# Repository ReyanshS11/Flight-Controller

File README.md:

# Express Flight Controller
Express is a feature-packed flight controller for drones.

## Key Features
- STM32H743VIT6 microcontroller for speed and performance
- ICM-45686 IMU for precise motion tracking
- BMP581 barometer for accurate altitude data
- NEO-M8U-06B GPS for pinpoint positioning
- Ra-02 RF transmitter for communication
- MicroSD slot for data storage
- USB-C port for program and data transfer
- 2s LiPo battery support and charging with BQ25887RGER
- Connectors for ESC and camera

## Design Features
- The complete flight controller fits within a 70x65mm space.
- Comprised of two layers, front and back copper
- Silkscreen for organization and ease of use

## Schematic and Design

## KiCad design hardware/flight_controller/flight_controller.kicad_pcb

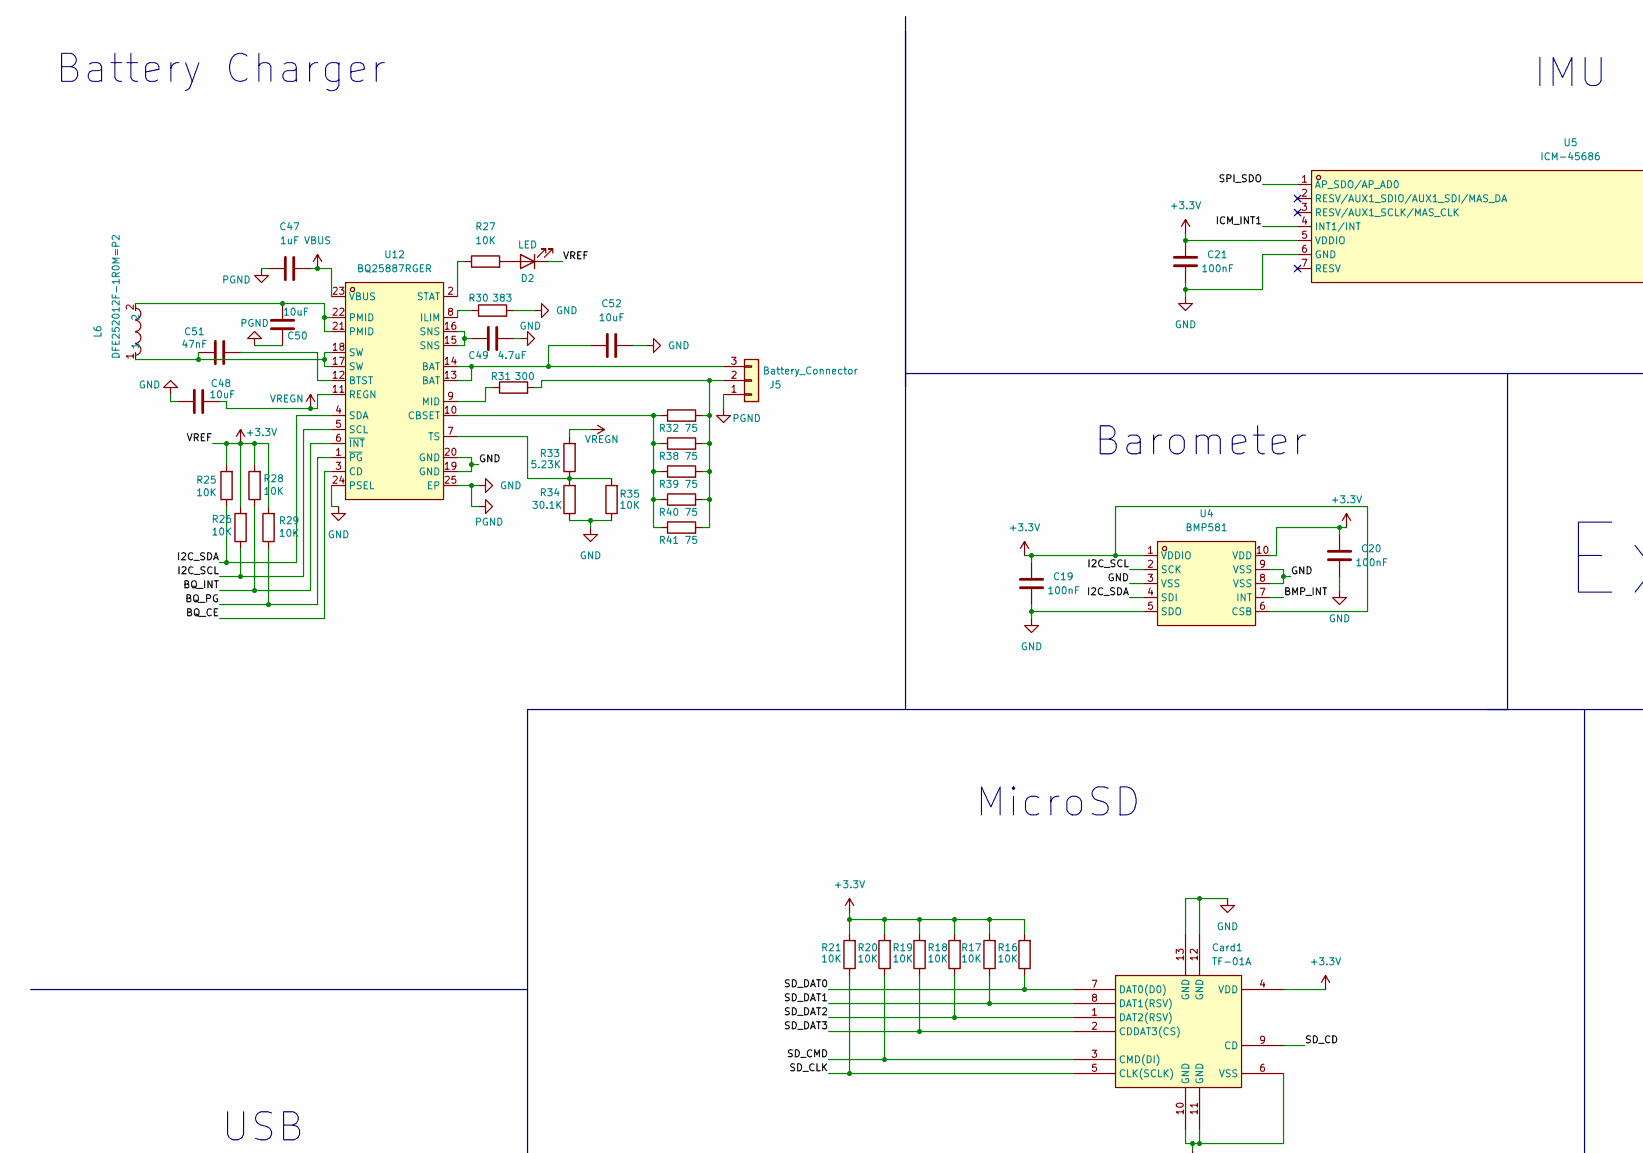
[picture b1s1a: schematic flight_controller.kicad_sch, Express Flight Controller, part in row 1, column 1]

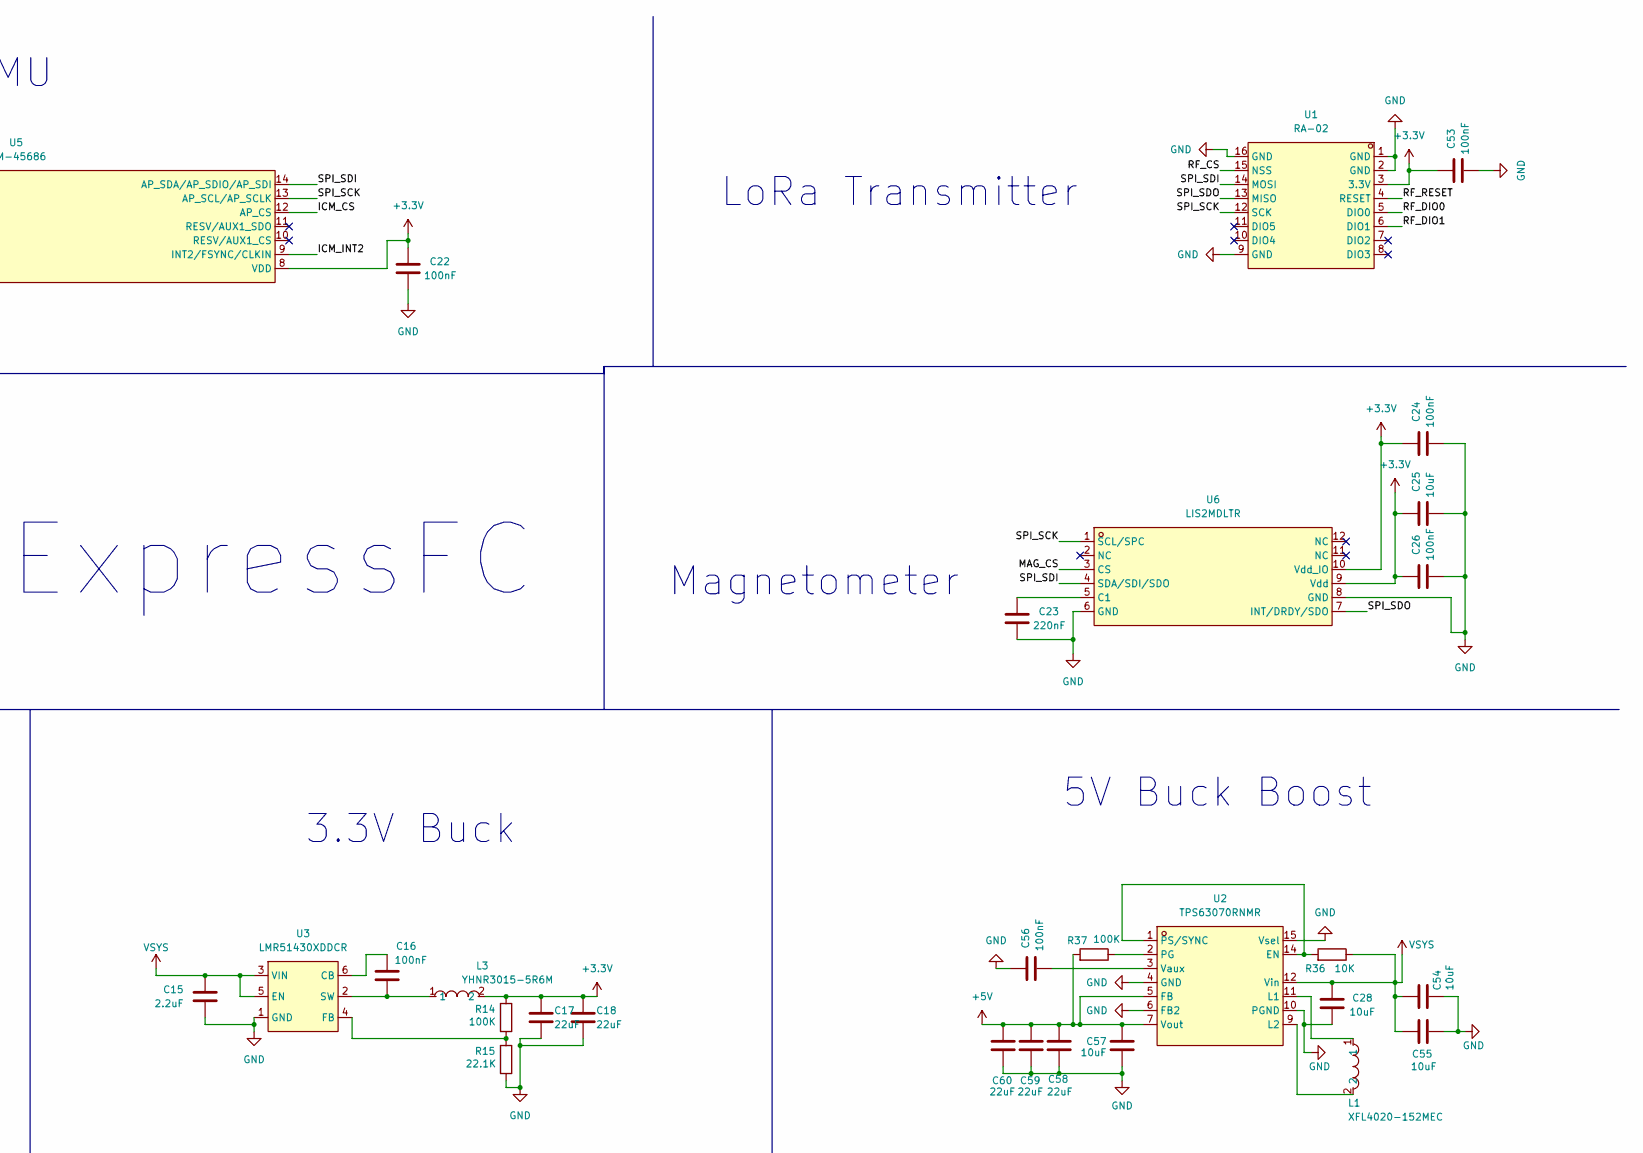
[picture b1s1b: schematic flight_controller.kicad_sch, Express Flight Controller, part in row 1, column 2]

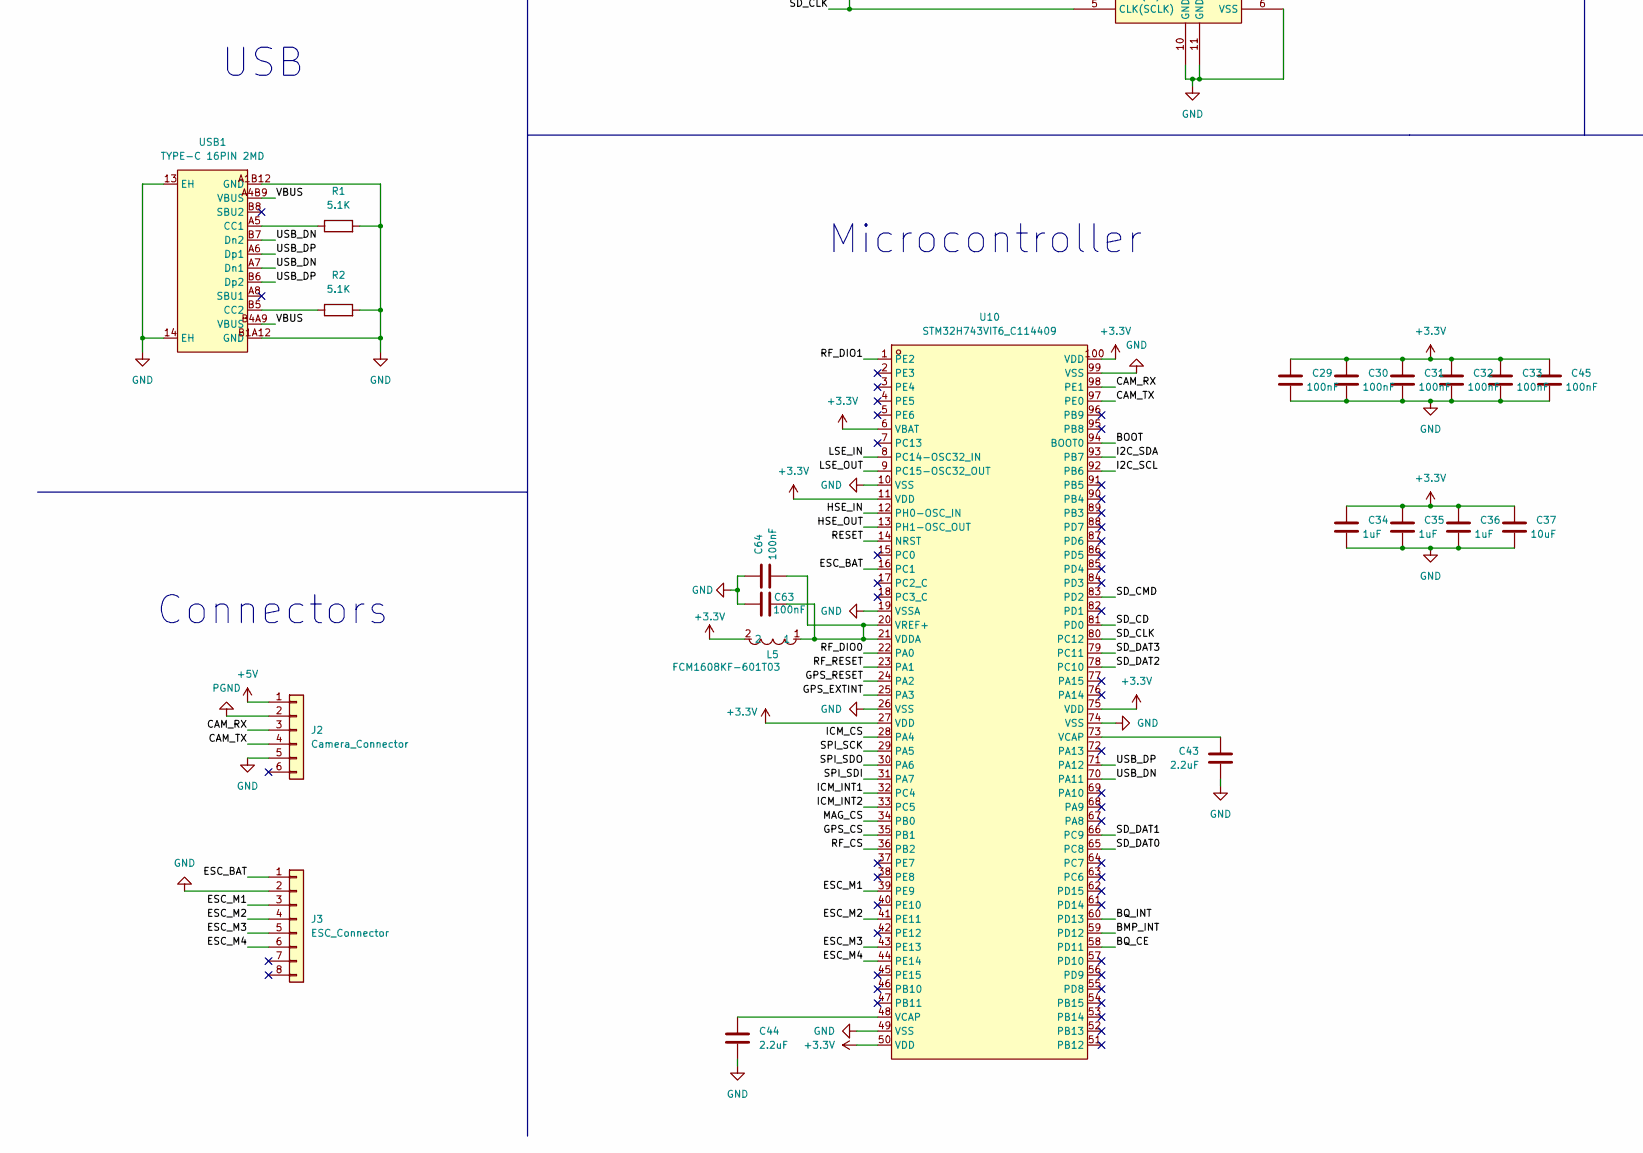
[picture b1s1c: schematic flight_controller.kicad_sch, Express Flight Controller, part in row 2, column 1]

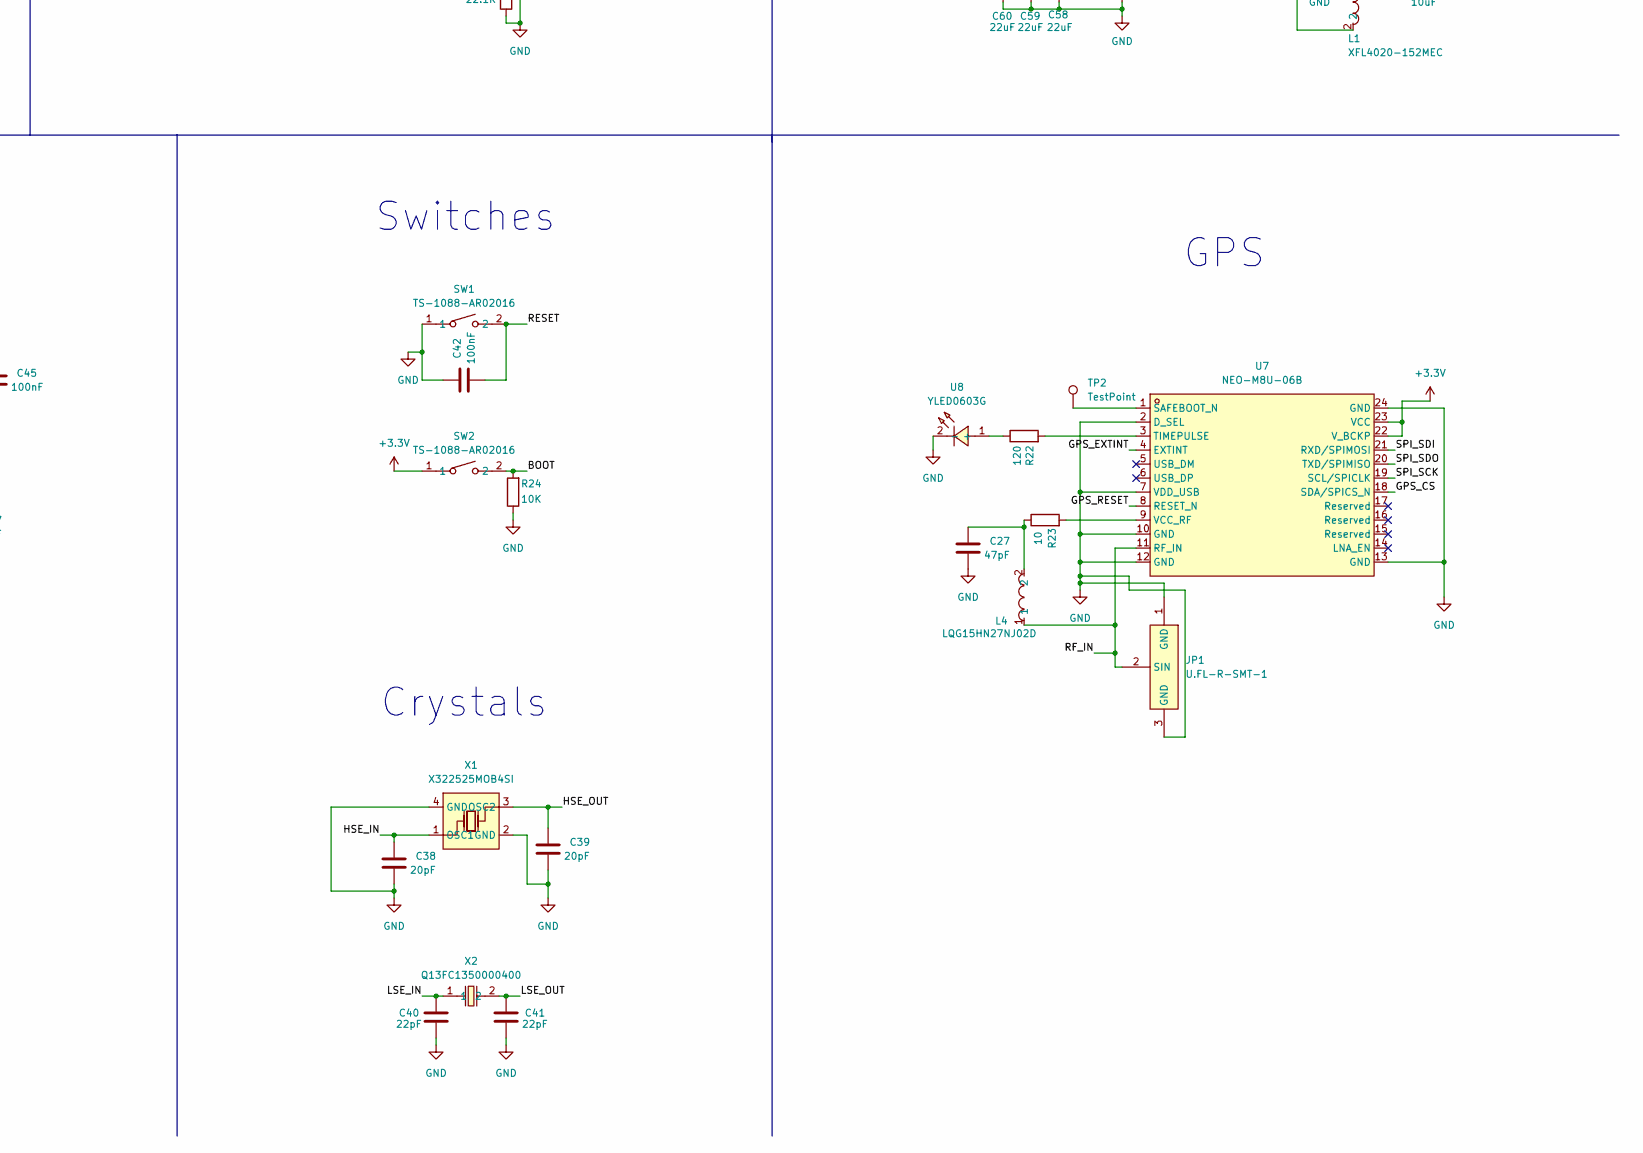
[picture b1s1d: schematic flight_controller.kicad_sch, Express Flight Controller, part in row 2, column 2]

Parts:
C15: 2.2uF; C_0603_1608Metric
C16, C19, C20, C21, C22, C24, C26, C29, C30, C31, C32, C33, C42, C45, C53, C63, C64: 100nF; C_0201_0603Metric
C17, C18, C58, C59, C60: 22uF; C_0805_2012Metric
C23: 220nF; C_0201_0603Metric
C25, C37, C48, C50, C57: 10uF; C_0402_1005Metric
C27: 47pF; C_0201_0603Metric
C28: 10uF; C_0201_0603Metric
C34, C35, C36, C47: 1uF; C_0402_1005Metric
C38, C39: 20pF; C_0201_0603Metric
C40, C41: 22pF; C_0201_0603Metric
C43, C44: 2.2uF; C_0402_1005Metric
C49: 4.7uF; C_0402_1005Metric
C51: 47nF; C_0201_0603Metric
C52: 10uF; C_0603_1608Metric
C54, C55: 10uF; C_0805_2012Metric
C56: 100nF; C_0402_1005Metric
Card1: TF-01A; TF-SMD_TF-01A; MPN TF-01A; LCSC Part C91145
D2: LED; LED_0402_1005Metric
J2: Camera_Connector; JST_SH_SM06B-SRSS-TB_1x06-1MP_P1.00mm_Horizontal
J3: ESC_Connector; JST_SH_SM08B-SRSS-TB_1x08-1MP_P1.00mm_Horizontal
J5: Battery_Connector; JST_XH_S3B-XH-A_1x03_P2.50mm_Horizontal
JP1: U.FL-R-SMT-1; ANT-SMD_UFL-R-SMT-1-10; MPN U.FL-R-SMT-1(10); LCSC Part C88373
L1: XFL4020-152MEC; IND-SMD_L4.0-W4.0-A; MPN XFL4020-152MEC; LCSC Part C3033018
L3: YHNR3015-5R6M; IND-SMD_L3.0-W3.0; MPN YHNR3015-5R6M; LCSC Part C18236327
L4: LQG15HN27NJ02D; L0402; MPN LQG15HN27NJ02D; LCSC Part C115488
L5: FCM1608KF-601T03; L0603; MPN FCM1608KF-601T03; LCSC Part C141723
L6: DFE252012F-1R0M=P2; L2520; MPN DFE252012F-1R0M=P2; LCSC Part C435392
R1, R2: 5.1K; R_0201_0603Metric
R14, R37: 100K; R_0603_1608Metric
R15: 22.1K; R_0402_1005Metric
R16, R17, R18, R19, R20, R21, R24, R25, R26, R27, R28, R29, R35, R36: 10K; R_0603_1608Metric
R22: 120; R_0201_0603Metric
R23: 10; R_0201_0603Metric
R30: 383; R_0603_1608Metric
R31: 300; R_0603_1608Metric
R32, R38, R39, R40, R41: 75; R_1206_3216Metric
R33: 5.23K; R_0603_1608Metric
R34: 30.1K; R_0603_1608Metric
SW1, SW2: TS-1088-AR02016; SW-SMD_L3.9-W3.0-P4.45; MPN TS-1088-AR02016; LCSC Part C720477
TP2: TestPoint; TestPoint_Pad_1.0x1.0mm
U1: RA-02; WIRELM-SMD_RA-02-BL; MPN Ra-02; LCSC Part C90039
U2: TPS63070RNMR; VQFN-15_L3.0-W2.5-P0.50-BL; MPN TPS63070RNMR; LCSC Part C109322
U3: LMR51430XDDCR; SOT-23-6_L2.9-W1.6-P0.95-LS2.8-BL; MPN LMR51430XDDCR; LCSC Part C5185863
U4: BMP581; LGA-10_L2.0-W2.0-P0.50-TL_BMP581; MPN BMP581; LCSC Part C5362283
U5: ICM-45686; LGA-14_L3.0-W2.5-P0.50-TL; MPN ICM-45686; LCSC Part C22459454
U6: LIS2MDLTR; VLGA-12_L2.0-W2.0-P0.50-BL; MPN LIS2MDLTR; LCSC Part C919695
U7: NEO-M8U-06B; GPSM-SMD_24P-L16.0-W12.2-P1.10-TL; MPN NEO-M8U-06B; LCSC Part C7009321
U8: YLED0603G; LED0603-FD; MPN YLED0603G; LCSC Part C19273151
U10: STM32H743VIT6_C114409; LQFP-100_L14.0-W14.0-P0.50-LS16.0-BL; MPN STM32H743VIT6; LCSC Part C114409
U12: BQ25887RGER; VFQFPN-24_L4.0-W4.0-P0.50-BL-EP2.8; MPN BQ25887RGER; LCSC Part C2761614
USB1: TYPE-C 16PIN 2MD; USB-C-SMD_TYPE-C-16PIN-2MD-073; MPN TYPE-C 16PIN 2MD(073); LCSC Part C2765186
X1: X322525MOB4SI; CRYSTAL-SMD_4P-L3.2-W2.5-BL; MPN X322525MOB4SI; LCSC Part C9006
X2: Q13FC1350000400; FC-135R_L3.2-W1.5; MPN Q13FC13500004; LCSC Part C32346

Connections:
+3.3V: C17.1, C18.1, C19.1, C20.1, C21.1, C22.1, C24.1, C25.1, C26.1, C29.1, C30.1, C31.1, C32.1, C33.1, C34.1, C35.1, C36.1, C37.1, C45.1, C53.1, Card1.4 (VDD), D2.1 (K), L3.2, L5.2, R14.2, R16.2, R17.2, R18.2, R19.2, R20.2, R21.2, R25.2, R26.2, R28.2, R29.2, SW2.1, U1.3 (3.3V), U4.1 (VDDIO), U4.6 (CSB), U4.10 (VDD), U5.5 (VDDIO), U5.8 (VDD), U6.9 (Vdd), U6.10 (Vdd_IO), U7.22 (V_BCKP), U7.23 (VCC), U10.6 (VBAT), U10.11 (VDD), U10.27 (VDD), U10.50 (VDD), U10.75 (VDD), U10.100 (VDD)
+5V: C57.1, C58.2, C59.2, C60.2, J2.1, R37.2, U2.5 (FB), U2.7 (Vout)
/BMP_INT: U4.7 (INT), U10.59 (PD12)
/BOOT: R24.2, SW2.2, U10.94 (BOOT0)
/BQ_CE: U10.58 (PD11), U12.3 (CD)
/BQ_INT: R28.1, U10.60 (PD13), U12.6 (~INT)
/BQ_PG: R29.1, U12.1 (~PG)
/CAM_RX: J2.3, U10.98 (PE1)
/CAM_TX: J2.4, U10.97 (PE0)
/ESC_BAT: J3.1, U10.16 (PC1)
/ESC_M1: J3.3, U10.39 (PE9)
/ESC_M2: J3.4, U10.41 (PE11)
/ESC_M3: J3.5, U10.43 (PE13)
/ESC_M4: J3.6, U10.44 (PE14)
/GPS_CS: U7.18 (SDA/SPICS_N), U10.35 (PB1)
/GPS_EXTINT: U7.4 (EXTINT), U10.25 (PA3)
/GPS_RESET: U7.8 (RESET_N), U10.24 (PA2)
/HSE_IN: C38.1, U10.12 (PH0-OSC_IN), X1.1 (OSC1)
/HSE_OUT: C39.1, U10.13 (PH1-OSC_OUT), X1.3 (OSC2)
/I2C_SCL: R26.1, U4.2 (SCK), U10.92 (PB6), U12.5 (SCL)
/I2C_SDA: R25.1, U4.4 (SDI), U10.93 (PB7), U12.4 (SDA)
/ICM_CS: U5.12 (AP_CS), U10.28 (PA4)
/ICM_INT1: U5.4 (INT1/INT), U10.32 (PC4)
/ICM_INT2: U5.9 (INT2/FSYNC/CLKIN), U10.33 (PC5)
/LSE_IN: C40.1, U10.8 (PC14-OSC32_IN), X2.1
/LSE_OUT: C41.1, U10.9 (PC15-OSC32_OUT), X2.2
/MAG_CS: U6.3 (CS), U10.34 (PB0)
/RESET: C42.2, SW1.2, U10.14 (NRST)
/RF_CS: U1.15 (NSS), U10.36 (PB2)
/RF_DIO0: U1.5 (DIO0), U10.22 (PA0)
/RF_DIO1: U1.6 (DIO1), U10.1 (PE2)
/RF_IN: JP1.2 (SIN), L4.1, U7.11 (RF_IN)
/RF_RESET: U1.4 (RESET), U10.23 (PA1)
/SD_CD: Card1.9 (CD), U10.81 (PD0)
/SD_CLK: Card1.5 (CLK(SCLK)), R21.1, U10.80 (PC12)
/SD_CMD: Card1.3 (CMD(DI)), R20.1, U10.83 (PD2)
/SD_DAT0: Card1.7 (DAT0(D0)), R16.1, U10.65 (PC8)
/SD_DAT1: Card1.8 (DAT1(RSV)), R17.1, U10.66 (PC9)
/SD_DAT2: Card1.1 (DAT2(RSV)), R18.1, U10.78 (PC10)
/SD_DAT3: Card1.2 (CDDAT3(CS)), R19.1, U10.79 (PC11)
/SPI_SCK: U1.12 (SCK), U5.13 (AP_SCL/AP_SCLK), U6.1 (SCL/SPC), U7.19 (SCL/SPICLK), U10.29 (PA5)
/SPI_SDI: U1.14 (MOSI), U5.14 (AP_SDA/AP_SDIO/AP_SDI), U6.4 (SDA/SDI/SDO), U7.21 (RXD/SPIMOSI), U10.31 (PA7)
/SPI_SDO: U1.13 (MISO), U5.1 (AP_SDO/AP_AD0), U6.7 (INT/DRDY/SDO), U7.20 (TXD/SPIMISO), U10.30 (PA6)
/USB_DN: U10.70 (PA11), USB1.A7 (Dn1), USB1.B7 (Dn2)
/USB_DP: U10.71 (PA12), USB1.A6 (Dp1), USB1.B6 (Dp2)
GND: C15.2, C17.2, C18.2, C19.2, C20.2, C21.2, C22.2, C23.2, C24.2, C25.2, C26.2, C27.2, C28.2, C29.2, C30.2, C31.2, C32.2, C33.2, C34.2, C35.2, C36.2, C37.2, C38.2, C39.2, C40.2, C41.2, C42.1, C43.2, C44.2, C45.2, C47.1, C48.1, C49.2, C50.1, C52.2, C53.2, C54.2, C55.2, C56.1, C57.2, C58.1, C59.1, C60.1, C63.1, C64.1, Card1.6 (VSS), Card1.10 (GND), Card1.11 (GND), Card1.12 (GND), Card1.13 (GND), J2.2, J2.5, J3.2, J5.1, JP1.1 (GND), JP1.3 (GND), R1.2, R2.2, R15.1, R24.1, R30.2, R34.1, R35.1, SW1.1, U1.1 (GND), U1.2 (GND), U1.9 (GND), U1.16 (GND), U2.4 (GND), U2.6 (FB2), U2.10 (PGND), U2.15 (Vsel), U3.1 (GND), U4.3 (VSS), U4.5 (SDO), U4.8 (VSS), U4.9 (VSS), U5.6 (GND), U6.6 (GND), U6.8 (GND), U7.2 (D_SEL), U7.7 (VDD_USB), U7.10 (GND), U7.12 (GND), U7.13 (GND), U7.24 (GND), U8.2 (-), U10.10 (VSS), U10.19 (VSSA), U10.26 (VSS), U10.49 (VSS), U10.74 (VSS), U10.99 (VSS), U12.19 (GND), U12.20 (GND), U12.24 (PSEL), U12.25 (EP), USB1.13 (EH), USB1.14 (EH), USB1.A1B12 (GND), USB1.B1A12 (GND), X1.2 (GND), X1.4 (GND)
unnamed: C27.1, L4.2, R23.1
unnamed: C43.1, U10.73 (VCAP)
unnamed: C44.1, U10.48 (VCAP)
unnamed: C49.1, U12.15 (SNS), U12.16 (SNS)
unnamed: C50.2, L6.2, U12.21 (PMID), U12.22 (PMID)
unnamed: C51.2, L6.1, U12.17 (SW), U12.18 (SW)
unnamed: D2.2 (A), R27.2
unnamed: J5.2, R31.2, R32.2, R38.2, R39.2, R40.2, R41.2
unnamed: C52.1, J5.3, U12.13 (BAT), U12.14 (BAT)
unnamed: R36.2, U2.1 (PS/SYNC), U2.14 (EN)
unnamed: L1.1, U2.11 (L1)
unnamed: L1.2, U2.9 (L2)
unnamed: R37.1, U2.2 (PG)
unnamed: C56.2, U2.3 (Vaux)
unnamed: C16.1, U3.6 (CB)
unnamed: R14.1, R15.2, U3.4 (FB)
unnamed: C16.2, L3.1, U3.2 (SW)
unnamed: C23.1, U6.5 (C1)
unnamed: TP2.1 (1_1), U7.1 (SAFEBOOT_N)
unnamed: R22.2, U7.3 (TIMEPULSE)
unnamed: R23.2, U7.9 (VCC_RF)
unnamed: R22.1, U8.1 (+)
unnamed: C63.2, C64.2, L5.1, U10.20 (VREF+), U10.21 (VDDA)
unnamed: C51.1, U12.12 (BTST)
unnamed: R32.1, R38.1, R39.1, R40.1, R41.1, U12.10 (CBSET)
unnamed: R30.1, U12.8 (ILIM)
unnamed: R31.1, U12.9 (MID)
unnamed: R27.1, U12.2 (STAT)
unnamed: R33.1, R34.2, R35.2, U12.7 (TS)
unnamed: R1.1, USB1.A5 (CC1)
unnamed: R2.1, USB1.B5 (CC2)
VBUS: C47.2, U12.23 (VBUS), USB1.A4B9 (VBUS), USB1.B4A9 (VBUS)
VREGN: C48.2, R33.2, U12.11 (REGN)
VSYS: C15.1, C28.1, C54.1, C55.1, R36.1, U2.12 (Vin), U3.3 (VIN), U3.5 (EN)

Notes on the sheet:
Microcontroller
Connectors
ExpressFC
GPS
Switches
Crystals
MicroSD
LoRa Transmitter
3.3V Buck
USB
Magnetometer
Barometer
5V Buck Boost
Battery Charger
IMU

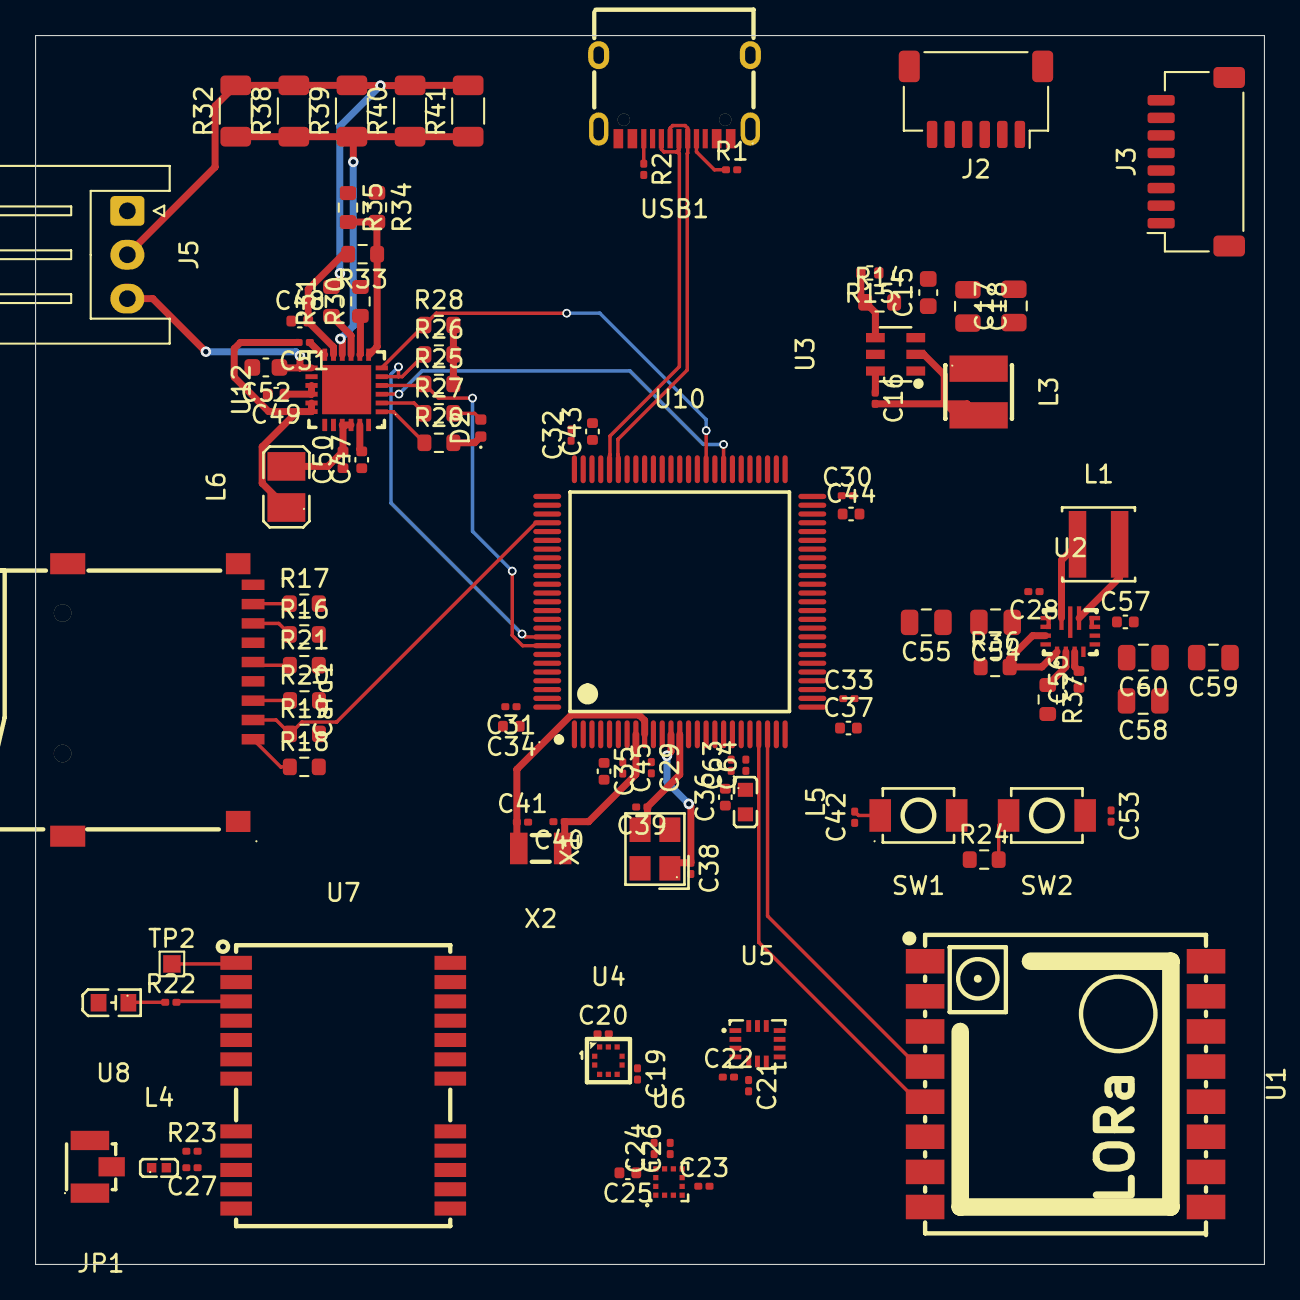
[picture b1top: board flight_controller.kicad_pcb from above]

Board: 4 copper layers, 70.0 x 70.0 mm, 104 parts (0 on the bottom side), 80 nets.

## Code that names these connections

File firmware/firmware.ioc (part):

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Mcu.Name=STM32H743VITx
Mcu.Package=LQFP100
Mcu.UserName=STM32H743VITx
PA0.GPIOParameters=GPIO_Label
PA0.GPIO_Label=RF_DIO0
PA0.Signal=GPXTI0
PA1.GPIOParameters=PinState,GPIO_Label
PA1.GPIO_Label=RF_RESET
PA1.PinState=GPIO_PIN_SET
PA1.Signal=GPIO_Output
PA11.Mode=Host_Only
PA11.Signal=USB_OTG_FS_DM
PA12.Mode=Host_Only
PA12.Signal=USB_OTG_FS_DP
PA2.GPIOParameters=PinState,GPIO_Label
PA2.GPIO_Label=GPS_RESET
PA2.PinState=GPIO_PIN_SET
PA2.Signal=GPIO_Output
PA3.GPIOParameters=GPIO_Label
PA3.GPIO_Label=GPS_EXTINT
PA3.Signal=GPXTI3
PA4.GPIOParameters=PinState,GPIO_PuPd,GPIO_Label
PA4.GPIO_Label=ICM_CS
PA4.GPIO_PuPd=GPIO_PULLUP
PA4.PinState=GPIO_PIN_SET
PA4.Signal=GPIO_Output
PA5.Mode=Full_Duplex_Master
PA5.Signal=SPI1_SCK
PA6.Mode=Full_Duplex_Master
PA6.Signal=SPI1_MISO
PA7.Mode=Full_Duplex_Master
PA7.Signal=SPI1_MOSI
PB0.GPIOParameters=PinState,GPIO_PuPd,GPIO_Label
PB0.GPIO_Label=MAG_CS
PB0.GPIO_PuPd=GPIO_PULLUP
PB0.PinState=GPIO_PIN_SET
PB0.Signal=GPIO_Output
PB1.GPIOParameters=PinState,GPIO_PuPd,GPIO_Label
PB1.GPIO_Label=GPS_CS
PB1.GPIO_PuPd=GPIO_PULLUP
PB1.PinState=GPIO_PIN_SET
PB1.Signal=GPIO_Output
PB2.GPIOParameters=PinState,GPIO_PuPd,GPIO_Label
PB2.GPIO_Label=RF_CS
PB2.GPIO_PuPd=GPIO_PULLUP
PB2.PinState=GPIO_PIN_SET
PB2.Signal=GPIO_Output
PB6.Mode=I2C
PB6.Signal=I2C1_SCL
PB7.Mode=I2C
PB7.Signal=I2C1_SDA
PC1.GPIOParameters=GPIO_Label
PC1.GPIO_Label=ESC_BAT
PC1.Signal=ADCx_INP11
PC10.Mode=SD_4_bits_Wide_bus
PC10.Signal=SDMMC1_D2
PC11.Mode=SD_4_bits_Wide_bus
PC11.Signal=SDMMC1_D3
PC12.Mode=SD_4_bits_Wide_bus
PC12.Signal=SDMMC1_CK
PC14-OSC32_IN\ (OSC32_IN).Mode=LSE-External-Oscillator
PC14-OSC32_IN\ (OSC32_IN).Signal=RCC_OSC32_IN
PC15-OSC32_OUT\ (OSC32_OUT).Mode=LSE-External-Oscillator
PC15-OSC32_OUT\ (OSC32_OUT).Signal=RCC_OSC32_OUT
PC4.GPIOParameters=GPIO_Label
PC4.GPIO_Label=ICM_INT1
PC4.Signal=GPXTI4
PC5.GPIOParameters=GPIO_Label
PC5.GPIO_Label=ICM_INT2
PC5.Signal=GPXTI5
PC8.Mode=SD_4_bits_Wide_bus
PC8.Signal=SDMMC1_D0
PC9.Mode=SD_4_bits_Wide_bus
PC9.Signal=SDMMC1_D1
PD0.GPIOParameters=GPIO_Label
PD0.GPIO_Label=SD_CS
PD0.Signal=GPIO_Input
PD11.GPIOParameters=GPIO_Label
PD11.GPIO_Label=BQ_CE
PD11.Signal=GPIO_Output
PD12.GPIOParameters=GPIO_Label
PD12.GPIO_Label=BMP_INT
PD12.Signal=GPXTI12
PD13.GPIOParameters=GPIO_Label
PD13.GPIO_Label=BQ_INT
PD13.Signal=GPXTI13
PD2.Mode=SD_4_bits_Wide_bus
PD2.Signal=SDMMC1_CMD
PE0.Mode=Asynchronous
PE0.Signal=UART8_RX
PE1.Mode=Asynchronous
PE1.Signal=UART8_TX
PE11.GPIOParameters=GPIO_Speed,GPIO_Label
PE11.GPIO_Label=ESC_M2
PE11.GPIO_Speed=GPIO_SPEED_FREQ_HIGH
PE11.Signal=S_TIM1_CH2
PE13.GPIOParameters=GPIO_Speed,GPIO_Label
PE13.GPIO_Label=ESC_M3
PE13.GPIO_Speed=GPIO_SPEED_FREQ_HIGH
PE13.Signal=S_TIM1_CH3
PE14.GPIOParameters=GPIO_Speed,GPIO_Label
PE14.GPIO_Label=ESC_M4
PE14.GPIO_Speed=GPIO_SPEED_FREQ_HIGH
PE14.Signal=S_TIM1_CH4
PE2.GPIOParameters=GPIO_Label
PE2.GPIO_Label=RF_DIO1
PE2.Signal=GPXTI2
PE9.GPIOParameters=GPIO_Speed,GPIO_Label
PE9.GPIO_Label=ESC_M1
PE9.GPIO_Speed=GPIO_SPEED_FREQ_HIGH
PE9.Signal=S_TIM1_CH1
PH0-OSC_IN\ (PH0).Mode=HSE-External-Oscillator
PH0-OSC_IN\ (PH0).Signal=RCC_OSC_IN
PH1-OSC_OUT\ (PH1).Mode=HSE-External-Oscillator
PH1-OSC_OUT\ (PH1).Signal=RCC_OSC_OUT
RCC.SYSCLKFreq_VALUE=400000000
RCC.SYSCLKSource=RCC_SYSCLKSOURCE_PLLCLK
board=custom
